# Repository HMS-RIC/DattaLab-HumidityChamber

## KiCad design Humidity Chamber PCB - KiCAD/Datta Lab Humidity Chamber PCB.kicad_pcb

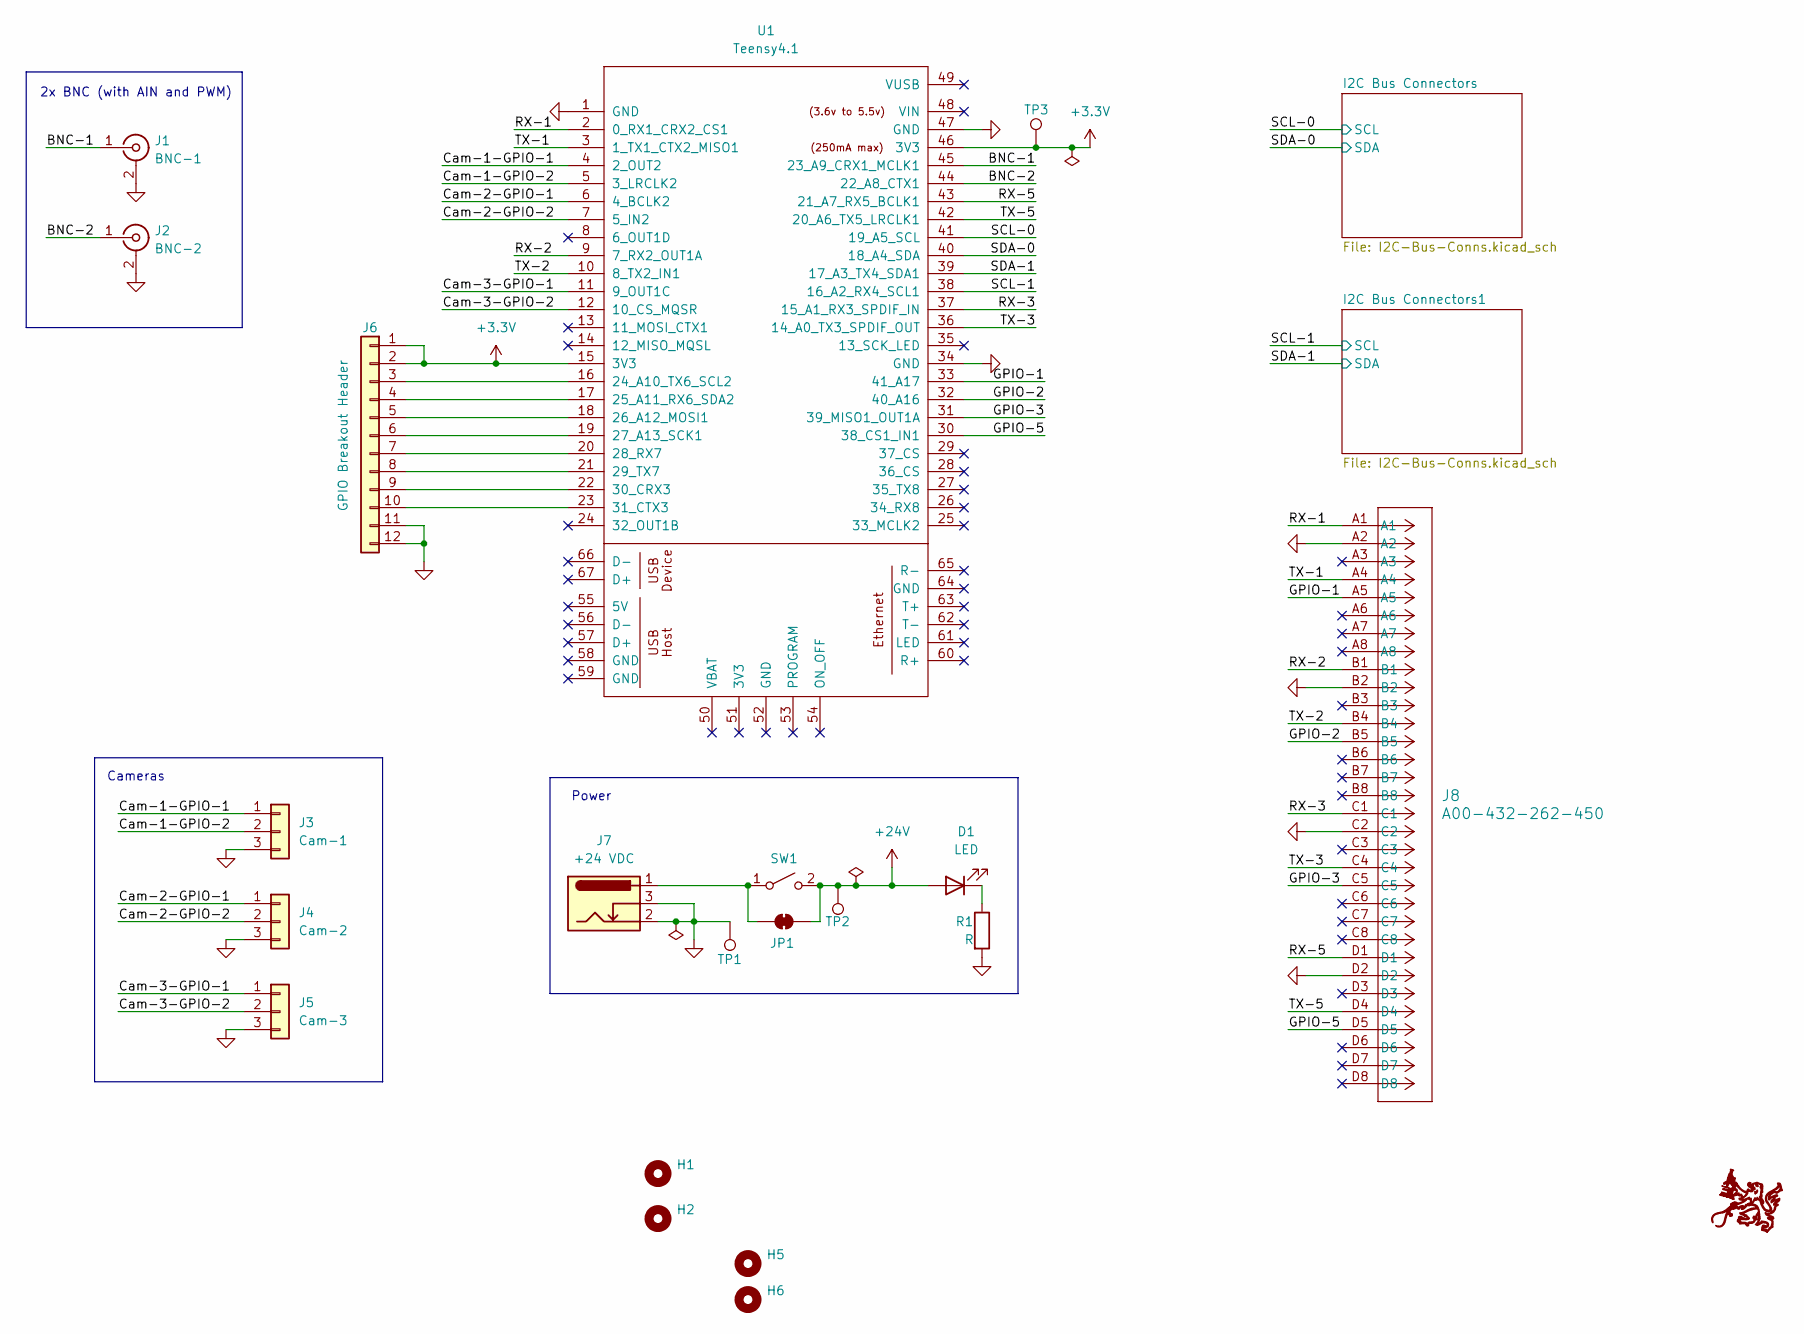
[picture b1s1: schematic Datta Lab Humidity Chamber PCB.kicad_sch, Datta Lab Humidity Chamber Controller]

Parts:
D1: LED; LED_D3.0mm
G1: RIC_Logo; RIC_Logo_15mm
H1, H2, H5, H6: MountingHole; MountingHole_3.2mm_M3
J1: BNC-1; BNC_Amphenol_B6252HB-NPP3G-50_Horizontal
J2: BNC-2; BNC_Amphenol_B6252HB-NPP3G-50_Horizontal
J3: Cam-1; PinSocket_1x03_P2.54mm_Vertical
J4: Cam-2; PinSocket_1x03_P2.54mm_Vertical
J5: Cam-3; PinSocket_1x03_P2.54mm_Vertical
J6: GPIO Breakout Header; PinHeader_1x12_P2.54mm_Vertical
J7: +24 VDC; BarrelJack_CUI_PJ-102AH_Horizontal
J8: A00-432-262-450; CONN_A00-432-262-450_EDA
JP1: SolderJumper_2_Open; SolderJumper-2_P1.3mm_Bridged_RoundedPad1.0x1.5mm
R1: R; R_Axial_DIN0207_L6.3mm_D2.5mm_P10.16mm_Horizontal
SW1: 500SSP1S1M6QEA; SW_500SSP1S1M6QEA
TP1: Gnd; TestPoint_Loop_D1.80mm_Drill1.0mm_Beaded
TP2: 24V; TestPoint_Loop_D1.80mm_Drill1.0mm_Beaded
TP3: 3V3; TestPoint_Loop_D1.80mm_Drill1.0mm_Beaded
U1: Teensy4.1; Teensy41_noInternalPins

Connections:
+3.3V: J6.1, J6.2, TP3.1, U1.15 (3V3), U1.46 (3V3); also elsewhere on the board
+24V: D1.2 (A), JP1.2 (B), SW1.2 (B), TP2.1; also elsewhere on the board
/BNC-1: J1.1 (In), U1.45 (23_A9_CRX1_MCLK1)
/BNC-2: J2.1 (In), U1.44 (22_A8_CTX1)
/Cam-1-GPIO-1: J3.1, U1.4 (2_OUT2)
/Cam-1-GPIO-2: J3.2, U1.5 (3_LRCLK2)
/Cam-2-GPIO-1: J4.1, U1.6 (4_BCLK2)
/Cam-2-GPIO-2: J4.2, U1.7 (5_IN2)
/Cam-3-GPIO-1: J5.1, U1.11 (9_OUT1C)
/Cam-3-GPIO-2: J5.2, U1.12 (10_CS_MQSR)
/GPIO-1: J8.A5, U1.33 (41_A17)
/GPIO-2: J8.B5, U1.32 (40_A16)
/GPIO-3: J8.C5, U1.31 (39_MISO1_OUT1A)
/GPIO-5: J8.D5, U1.30 (38_CS1_IN1)
/RX-1: J8.A1, U1.2 (0_RX1_CRX2_CS1)
/RX-2: J8.B1, U1.9 (7_RX2_OUT1A)
/RX-3: J8.C1, U1.37 (15_A1_RX3_SPDIF_IN)
/RX-5: J8.D1, U1.43 (21_A7_RX5_BCLK1)
/SCL-0: U1.41 (19_A5_SCL); also elsewhere on the board
/SCL-1: U1.38 (16_A2_RX4_SCL1); also elsewhere on the board
/SDA-0: U1.40 (18_A4_SDA); also elsewhere on the board
/SDA-1: U1.39 (17_A3_TX4_SDA1); also elsewhere on the board
/TX-1: J8.A4, U1.3 (1_TX1_CTX2_MISO1)
/TX-2: J8.B4, U1.10 (8_TX2_IN1)
/TX-3: J8.C4, U1.36 (14_A0_TX3_SPDIF_OUT)
/TX-5: J8.D4, U1.42 (20_A6_TX5_LRCLK1)
GND: J1.2 (Ext), J2.2 (Ext), J3.3, J4.3, J5.3, J6.11, J6.12, J7.2, J7.3, J8.A2, J8.B2, J8.C2, J8.D2, R1.2, TP1.1, U1.1 (GND), U1.34 (GND), U1.47 (GND); also elsewhere on the board
unnamed: D1.1 (K), R1.1
unnamed: J6.3, U1.16 (24_A10_TX6_SCL2)
unnamed: J6.4, U1.17 (25_A11_RX6_SDA2)
unnamed: J6.5, U1.18 (26_A12_MOSI1)
unnamed: J6.6, U1.19 (27_A13_SCK1)
unnamed: J6.7, U1.20 (28_RX7)
unnamed: J6.8, U1.21 (29_TX7)
unnamed: J6.9, U1.22 (30_CRX3)
unnamed: J6.10, U1.23 (31_CTX3)
unnamed: J7.1, JP1.1 (A), SW1.1 (A)

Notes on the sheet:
Power
Cameras
2x BNC (with AIN and PWM)

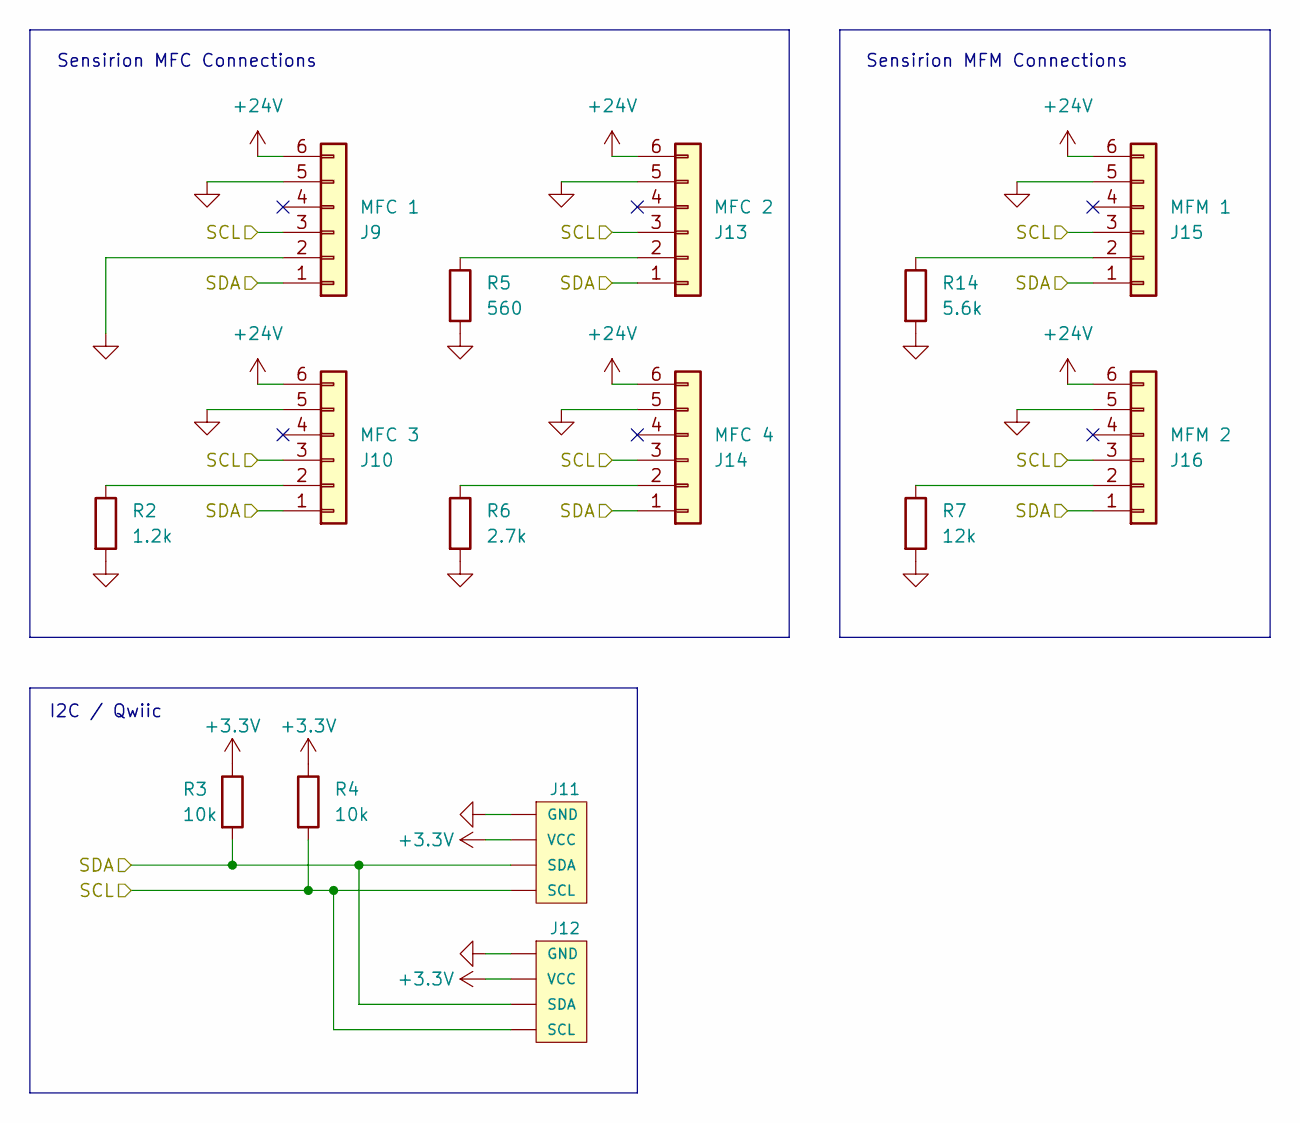
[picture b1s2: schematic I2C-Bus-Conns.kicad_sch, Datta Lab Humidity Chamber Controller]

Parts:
J9: MFC 1; CONN_50556806xx_MOL
J10: MFC 3; CONN_50556806xx_MOL
J11, J12: I2C_STANDARDQWIIC; 1X04_1MM_RA
J13: MFC 2; CONN_50556806xx_MOL
J14: MFC 4; CONN_50556806xx_MOL
J15: MFM 1; CONN_50556806xx_MOL
J16: MFM 2; CONN_50556806xx_MOL
R2: 1.2k; R_Axial_DIN0207_L6.3mm_D2.5mm_P10.16mm_Horizontal
R3, R4: 10k; R_Axial_DIN0207_L6.3mm_D2.5mm_P10.16mm_Horizontal
R5: 560; R_Axial_DIN0207_L6.3mm_D2.5mm_P10.16mm_Horizontal
R6: 2.7k; R_Axial_DIN0207_L6.3mm_D2.5mm_P10.16mm_Horizontal
R7: 12k; R_Axial_DIN0207_L6.3mm_D2.5mm_P10.16mm_Horizontal
R14: 5.6k; R_Axial_DIN0207_L6.3mm_D2.5mm_P10.16mm_Horizontal

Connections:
+3.3V: J11.2 (VCC), J12.2 (VCC), R3.1, R4.1; also elsewhere on the board
+24V: J9.6, J10.6, J13.6, J14.6, J15.6, J16.6; also elsewhere on the board
/SCL-0: J9.3, J10.3, J11.4 (SCL), J12.4 (SCL), J13.3, J14.3, J15.3, J16.3, R4.2; also elsewhere on the board
/SDA-0: J9.1, J10.1, J11.3 (SDA), J12.3 (SDA), J13.1, J14.1, J15.1, J16.1, R3.2; also elsewhere on the board
GND: J9.2, J9.5, J10.5, J11.1 (GND), J12.1 (GND), J13.5, J14.5, J15.5, J16.5, R2.2, R5.2, R6.2, R7.2, R14.2; also elsewhere on the board
unnamed: J10.2, R2.1
unnamed: J13.2, R5.1
unnamed: J14.2, R6.1
unnamed: J15.2, R14.1
unnamed: J16.2, R7.1

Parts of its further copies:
J17: MFC 1; CONN_50556806xx_MOL
J18: MFC 3; CONN_50556806xx_MOL
J19, J20: I2C_STANDARDQWIIC; 1X04_1MM_RA
J21: MFC 2; CONN_50556806xx_MOL
J22: MFC 4; CONN_50556806xx_MOL
J23: MFM 1; CONN_50556806xx_MOL
J24: MFM 2; CONN_50556806xx_MOL
R8: 1.2k; R_Axial_DIN0207_L6.3mm_D2.5mm_P10.16mm_Horizontal
R9, R10: 10k; R_Axial_DIN0207_L6.3mm_D2.5mm_P10.16mm_Horizontal
R11: 560; R_Axial_DIN0207_L6.3mm_D2.5mm_P10.16mm_Horizontal
R12: 2.7k; R_Axial_DIN0207_L6.3mm_D2.5mm_P10.16mm_Horizontal
R13: 12k; R_Axial_DIN0207_L6.3mm_D2.5mm_P10.16mm_Horizontal
R15: 5.6k; R_Axial_DIN0207_L6.3mm_D2.5mm_P10.16mm_Horizontal

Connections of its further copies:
+3.3V: J19.2 (VCC), J20.2 (VCC), R9.1, R10.1; also elsewhere on the board
+24V: J17.6, J18.6, J21.6, J22.6, J23.6, J24.6; also elsewhere on the board
/SCL-1: J17.3, J18.3, J19.4 (SCL), J20.4 (SCL), J21.3, J22.3, J23.3, J24.3, R10.2; also elsewhere on the board
/SDA-1: J17.1, J18.1, J19.3 (SDA), J20.3 (SDA), J21.1, J22.1, J23.1, J24.1, R9.2; also elsewhere on the board
GND: J17.2, J17.5, J18.5, J19.1 (GND), J20.1 (GND), J21.5, J22.5, J23.5, J24.5, R8.2, R11.2, R12.2, R13.2, R15.2; also elsewhere on the board
unnamed: J18.2, R8.1
unnamed: J21.2, R11.1
unnamed: J22.2, R12.1
unnamed: J23.2, R15.1
unnamed: J24.2, R13.1

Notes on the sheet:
Sensirion MFC Connections
I2C / Qwiic
Sensirion MFM Connections

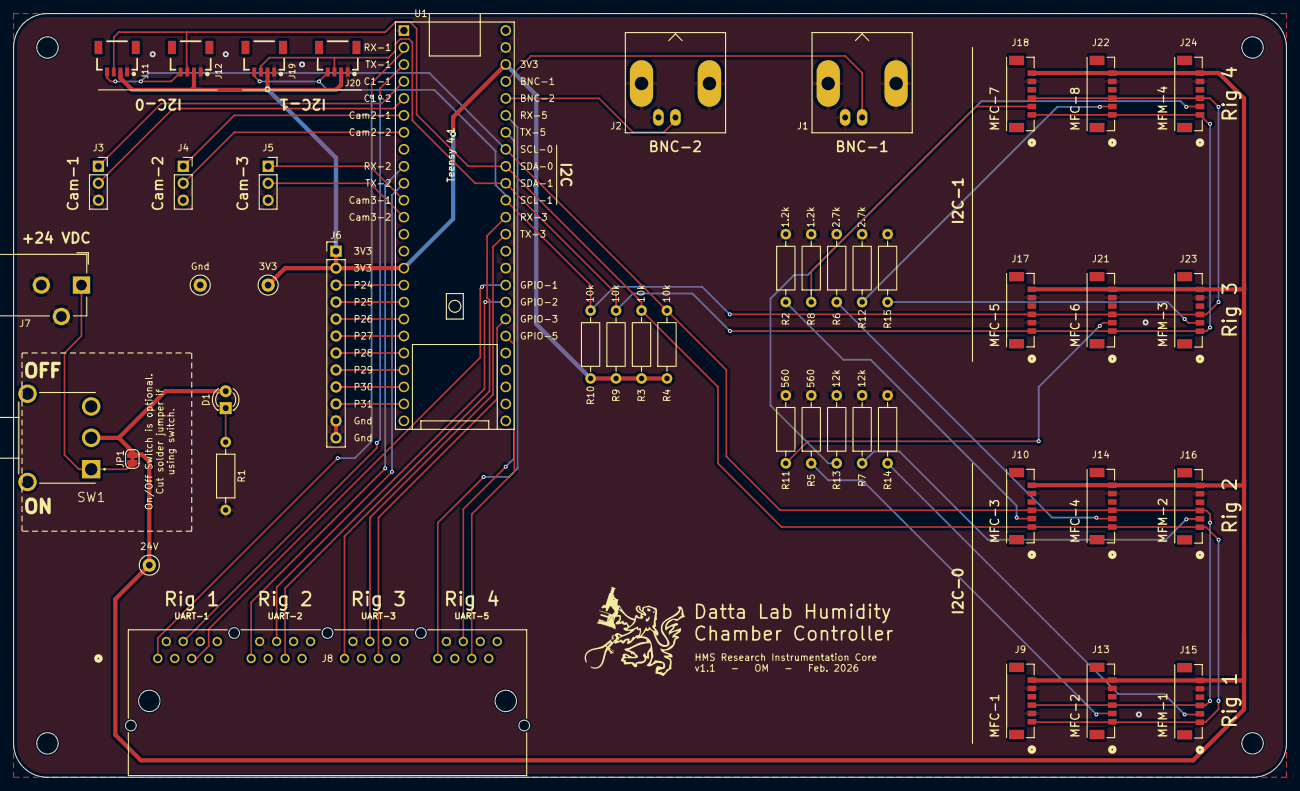
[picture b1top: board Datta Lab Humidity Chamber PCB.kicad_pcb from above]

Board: 2 copper layers, 190.5 x 114.3 mm, 51 parts (0 on the bottom side), 47 nets.

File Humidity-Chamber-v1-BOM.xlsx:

|  | Datta Lab Humidity Chamber Controller: Part List
Item | PCB Label | Item | Value | Vendor | Part # | Qty | Price | Total |  | Notes
1 |  | Sensirion SFC6000D-5slm |  | Digikey | 1649-SFC6000D-5SLM-ND | 8 | 372 | 2976
2 |  | Sensirion MFM |  | Digikey | 1649-SFM6000D-5SLM-ND | 4 | 218 | 872
3 |  | MFC Cables |  | Digikey | WM17189-ND | 12 | 2.5 | 30
4 |  | 1/4" Tubing Adptor for MFCs (10 pack) |  | Digikey | 2171-QSPK18-1/4-U-ND | 3 | 24.3 | 72.900000000000006 |  | Helpful if using 1/4" OD Tubing; By default MFCs will work with 6mm OD tubing
5 |  | PCB |  | Advanced Circuits |  | 1 | 33 | 33 |  | Minimum order of 3 to qualify for the $33 special
6 | D1 | LED 3mm |  | Digikey | 732-5008-ND | 1 | 0.15 | 0.15 |  | Optional, Any comparable part is fine
7 | J1–2 | BNC Connector |  | Digikey | WM5514-ND | 2 | 4.6900000000000004 | 9.3800000000000008 |  | Or try A32245-ND
8 | J3–5 | 1x3 Header |  | Digikey | A19430-ND | 3 |  | 0
9 | J6 | 1x12 Socket |  | Digikey | S7045-ND | 1 |  | 0
10 | J7 | Barrel Jack |  | Digikey | CP-202A-ND | 1 | 0.61 | 0.61
11 | J8 | 4-way RJ-45 Connector |  | Digikey | 151-1120-ND | 1 | 4.12 | 4.12
12 | J9–10, J13–18, J21–24 | Senserion connectors | Molex 5055680681 | Digikey | WM26835CT-ND | 12 | 1.02 | 12.24
13 | J11,J12,J19,J20 | Qwiic connector |  | Digikey | 455-SM04B-SRSS-TBCT-ND | 1 | 0.52 | 0.52 |  | Or try A32245-ND
14 | R1 | Resistor | 2k |  |  | 1 |  | 0
15 | R2,R8 | Resistor | 1.2k |  |  | 2 |  | 0
16 | R3,R4,R9,R10 | Resistor | 10k |  |  | 4 |  | 0
17 | R5,R7,R11,R13 | Resistor | 560 |  |  | 4 |  | 0
18 | R6,R12 | Resistor | 2.7k |  |  | 2 |  | 0
19 | SW1 | Switch | 500SSP1S1M6QEA | Digikey | EG2478-ND | 1 | 3.92 | 3.92 |  | Optional; Be sure to cut solder jumper (JP1) if using switch
20 | U1 | Teensy 4.1 with Headers |  | Sparkfun | DEV-16997 | 1 | 26.8 | 26.8
21 |  | 1x24 Socket |  | Digikey | S7057-ND | 2 | 1.35 | 2.7
22 |  | Power Supply 24V DC 2A |  | Digikey | 364-1286-ND | 1 | 19.38 | 19.38
23 |  | Standoffs |  | McMaster | 92745A320 | 4 | 0.63 | 2.52
 |  |  |  |  |  |  | TOTAL | 4066.2400000000002

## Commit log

2026-01-07 Restructure directories
2026-01-14 Rearrange board layout per Brian's feedback
2026-01-14 Routed all traces
2026-01-14 Minor cosmetic adjustments
2026-01-14 Rounded PCB corners; More minor fixes
2026-01-14 Simplified 24V traces
2026-01-14 Generate Gerbers; A few small tweaks
2026-01-14 Update BOM
2026-01-27 Start v1.1. Fix address resistors for MFMs
